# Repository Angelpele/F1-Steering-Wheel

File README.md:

# 🏎️ F1 Steering Wheel

This project is a **custom-made F1-style steering wheel** designed and built entirely from scratch, featuring a **custom PCB**, advanced input/output handling, and a rigid mechanical structure optimized for sim racing or small racing karts.

---

## 🛠️ Electronics & PCB Design

The steering wheel is built around a **custom-designed PCB** using an **ESP32-C6 DevKitC-1** as the main controller, providing high performance and wireless capabilities.

### Main Electronic Features

| Component | Description |
|---------|-------------|
| **ESP32-C6 DevKitC-1** | Main microcontroller handling inputs, logic, and communication |
| **74LS154 Decoder** | 4-to-16 line decoder used to drive LED array |
| **15 LEDs (RGB Groups)** | Divided into 3 groups of 5 LEDs (Green, Red, Blue) |
| **4-Digit 7-Segment Display** | Displays speed, gear, or system information |
| **8 Buttons (Resistor Ladder)** | All buttons read through a single ADC pin |
| **2 Potentiometers** | Center mounted, using voltage divider for analog input |
| **Buzzer** | Return sound feedback to the user reacting to different variables |
| **External Sensor Support** | Designed for external NTC temperature sensor and Hall-effect sensor inputs|
| **Custom Buttons PCB** | Top-mounted buttons integrated into the housing |

The **15 LEDs**, controlled via the **74LS154 decoder**, provide real-time visual feedback:
- **Green LEDs** → Speed or system status  
- **Red LEDs** → Engine RPM / rev-up indication  
- **Blue LEDs** → Custom functions or gear indicators  

The decoder uses **4 control lines** to efficiently manage all LED outputs.

The **8 buttons** are arranged with a resistor ladder configuration, reading all the possible values with an ADC converter (analog input).

📄 Find the **Circuit Schematic** right below:

<p align="center">
  
</p>

---

## ⚙️ Mechanical Design

The entire mechanical structure was **designed from scratch in Fusion 360**, prioritizing rigidity, modularity, and professional finish.

### Structural Overview

1. **Lower Case**
   - Houses most electronic components.
   - Rear sockets allow bolts to be inserted flush with the surface.
   - Enables clean and solid assembly.

2. **Steel Reinforcement Plate**
   - Water-jet cut steel middle plate.
   - Provides structural rigidity and torsional strength.
   - Acts as the main load-bearing core.

3. **TPU Handles**
   - Designed in **two parts per side**.
   - Bolted directly to the internal steel structure.
   - Flexible yet durable for comfortable grip.

4. **PCB Mounting**
   - Custom PCB is mounted on top of the steel plate.
   - Electrically isolated to prevent short circuits.
   - Secured using threaded inserts.

5. **Top Case & Buttons**
   - Top enclosure holds the custom-made buttons.
   - Assembled using **threaded inserts melted into the plastic**.
   - All components are bolted together for maximum durability.

---

## 🚀 Project Goals

- Realistic **F1-style input device**
- Robust **mechanical and electrical integration**
- Support for additional external sensors
- Internal steel structure for proper soldering to external axes

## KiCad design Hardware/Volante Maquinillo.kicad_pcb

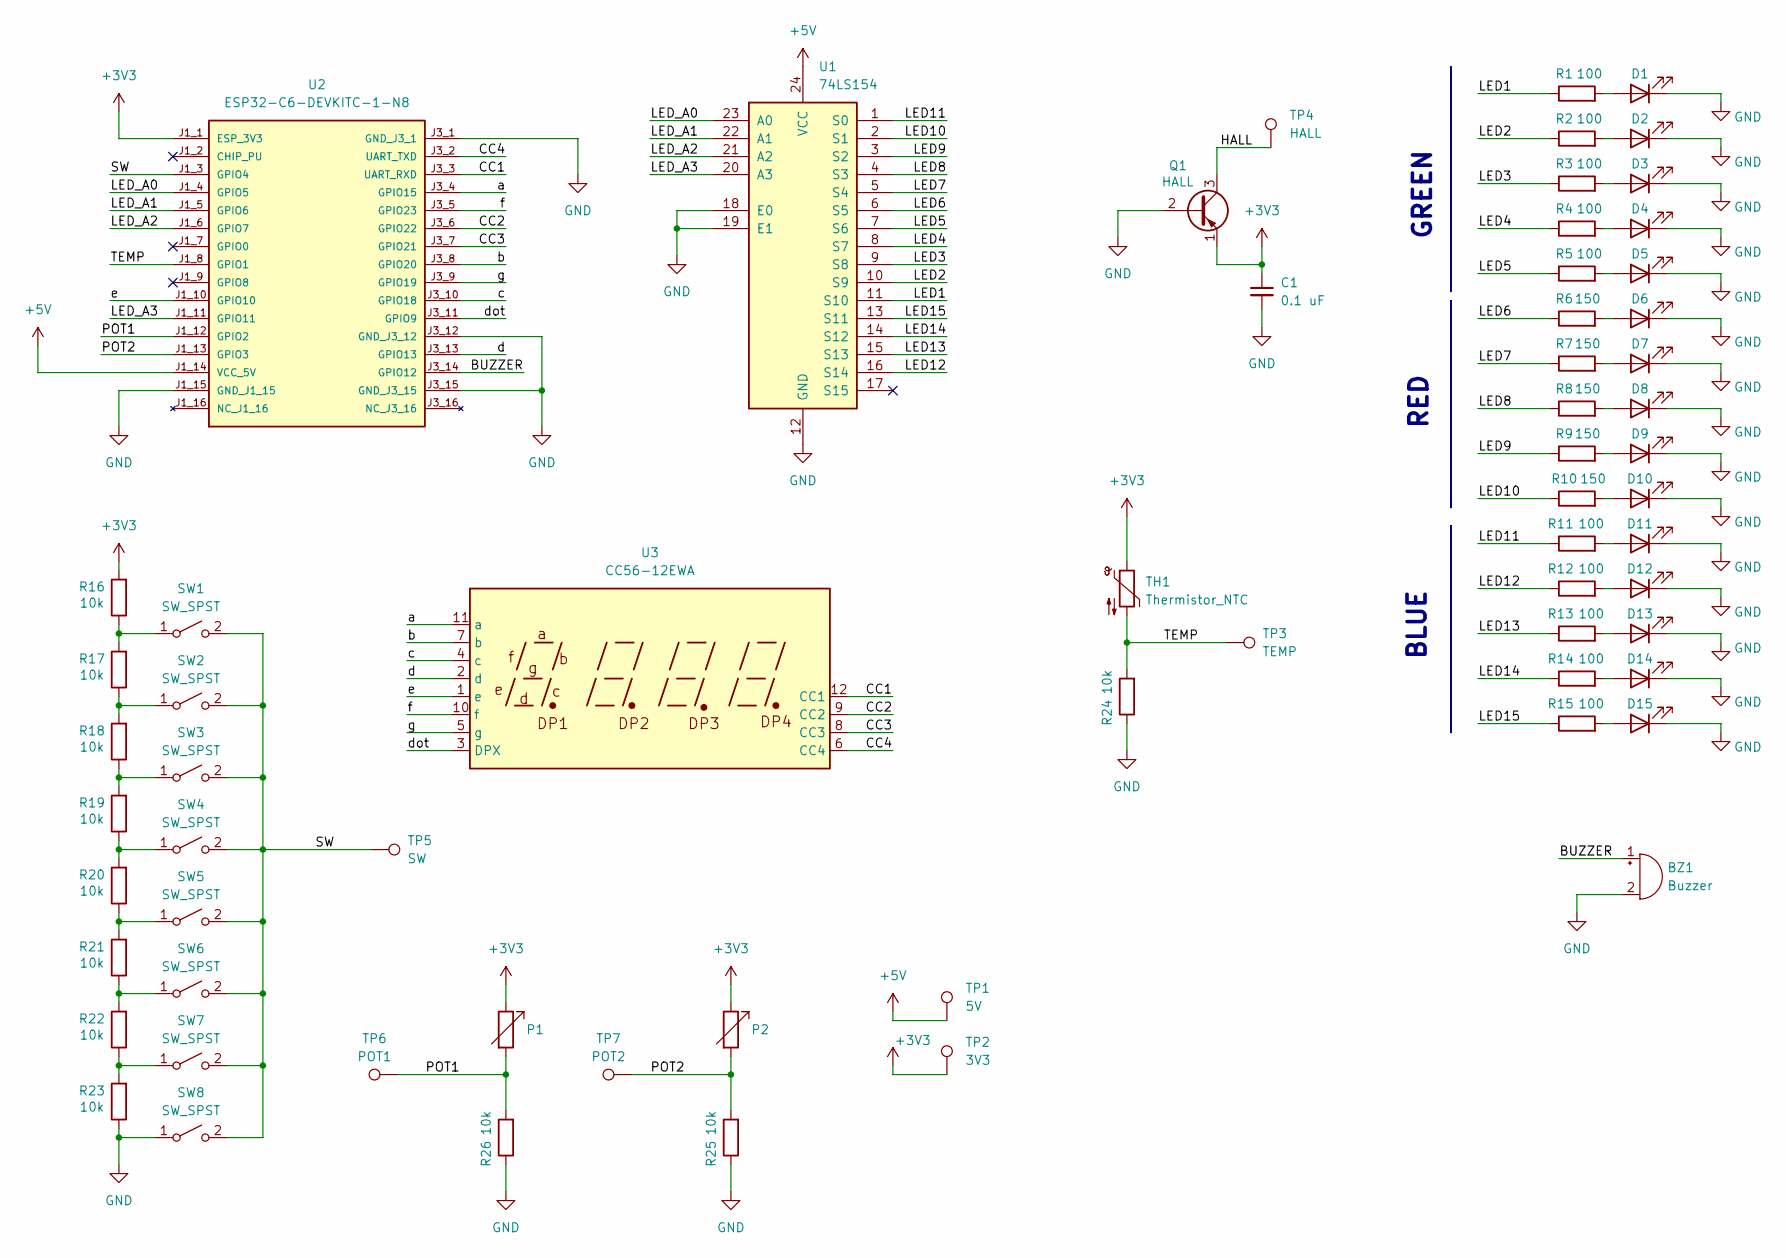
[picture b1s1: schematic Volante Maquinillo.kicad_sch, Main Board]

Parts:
BZ1: Buzzer; Buzzer_12x9.5RM7.6
C1: 0.1 uF; C_0805_2012Metric
D1, D2, D3, D4, D5, D6, D7, D8, D9, D10, D11, D12, D13, D14, D15: LED; LED_Cree-PLCC4_3.2x2.8mm_CCW
P1, P2: R_Variable; Potentiometer_ACP_CA9-V10_Vertical_Hole
Q1: HALL; TO-92Flat
R1, R2, R3, R4, R5, R11, R12, R13, R14, R15: 100; R_0805_2012Metric
R6, R7, R8, R9, R10: 150; R_0805_2012Metric
R16, R17, R18, R19, R20, R21, R22, R23, R24, R25, R26: 10k; R_0805_2012Metric
SW1, SW2, SW3, SW4, SW5, SW6, SW7, SW8: SW_SPST; SW_TS02-66-60-BK-100-LCR-D
TH1: Thermistor_NTC; PinHeader_1x02_P2.54mm_Vertical
TP1: 5V; TestPoint_Pad_D1.0mm
TP2: 3V3; TestPoint_Pad_D1.0mm
TP3: TEMP; TestPoint_Pad_D1.0mm
TP4: HALL; TestPoint_Pad_D1.0mm
TP5: SW; TestPoint_Pad_D1.0mm
TP6: POT1; TestPoint_Pad_D1.0mm
TP7: POT2; TestPoint_Pad_D1.0mm
U1: 74LS154; TSSOP-24_4.4x7.8mm_P0.65mm
U2: ESP32-C6-DEVKITC-1-N8; MODULE_ESP32-C6-DEVKITC-1-N8; PARTREV 1.3
U3: CC56-12EWA; CA56-12EWA

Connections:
+3V3: C1.1, P1.1, P2.1, Q1.1 (E), R16.2, TH1.1, TP2.1, U2.J1_1 (ESP_3V3)
+5V: TP1.1, U1.24 (VCC), U2.J1_14 (VCC_5V)
/BUZZER: BZ1.1 (+), U2.J3_14 (GPIO12)
/CC1: U2.J3_3 (UART_RXD), U3.12 (CC1)
/CC2: U2.J3_6 (GPIO22), U3.9 (CC2)
/CC3: U2.J3_7 (GPIO21), U3.8 (CC3)
/CC4: U2.J3_2 (UART_TXD), U3.6 (CC4)
/HALL: Q1.3 (C), TP4.1
/LED1: R1.1, U1.11 (S10)
/LED2: R2.1, U1.10 (S9)
/LED3: R3.1, U1.9 (S8)
/LED4: R4.1, U1.8 (S7)
/LED5: R5.1, U1.7 (S6)
/LED6: R6.1, U1.6 (S5)
/LED7: R7.1, U1.5 (S4)
/LED8: R8.1, U1.4 (S3)
/LED9: R9.1, U1.3 (S2)
/LED10: R10.1, U1.2 (S1)
/LED11: R11.1, U1.1 (S0)
/LED12: R12.1, U1.16 (S14)
/LED13: R13.1, U1.15 (S13)
/LED14: R14.1, U1.14 (S12)
/LED15: R15.1, U1.13 (S11)
/LED_A0: U1.23 (A0), U2.J1_4 (GPIO5)
/LED_A1: U1.22 (A1), U2.J1_5 (GPIO6)
/LED_A2: U1.21 (A2), U2.J1_6 (GPIO7)
/LED_A3: U1.20 (A3), U2.J1_11 (GPIO11)
/POT1: P1.2, R26.2, TP6.1, U2.J1_12 (GPIO2)
/POT2: P2.2, R25.2, TP7.1, U2.J1_13 (GPIO3)
/SW: SW1.2 (B), SW2.2 (B), SW3.2 (B), SW4.2 (B), SW5.2 (B), SW6.2 (B), SW7.2 (B), SW8.2 (B), TP5.1, U2.J1_3 (GPIO4)
/TEMP: R24.2, TH1.2, TP3.1, U2.J1_8 (GPIO1)
/a: U2.J3_4 (GPIO15), U3.11 (a)
/b: U2.J3_8 (GPIO20), U3.7 (b)
/c: U2.J3_10 (GPIO18), U3.4 (c)
/d: U2.J3_13 (GPIO13), U3.2 (d)
/dot: U2.J3_11 (GPIO9), U3.3 (DPX)
/e: U2.J1_10 (GPIO10), U3.1 (e)
/f: U2.J3_5 (GPIO23), U3.10 (f)
/g: U2.J3_9 (GPIO19), U3.5 (g)
GND: BZ1.2 (-), C1.2, D1.1 (K), D2.1 (K), D3.1 (K), D4.1 (K), D5.1 (K), D6.1 (K), D7.1 (K), D8.1 (K), D9.1 (K), D10.1 (K), D11.1 (K), D12.1 (K), D13.1 (K), D14.1 (K), D15.1 (K), Q1.2 (B), R23.1, R24.1, R25.1, R26.1, SW8.1 (A), U1.12 (GND), U1.18 (E0), U1.19 (E1), U2.J1_15 (GND_J1_15), U2.J3_1 (GND_J3_1), U2.J3_12 (GND_J3_12), U2.J3_15 (GND_J3_15)
unnamed: D1.2 (A), R1.2
unnamed: D2.2 (A), R2.2
unnamed: D3.2 (A), R3.2
unnamed: D4.2 (A), R4.2
unnamed: D5.2 (A), R5.2
unnamed: D6.2 (A), R6.2
unnamed: D7.2 (A), R7.2
unnamed: D8.2 (A), R8.2
unnamed: D9.2 (A), R9.2
unnamed: D10.2 (A), R10.2
unnamed: D11.2 (A), R11.2
unnamed: D12.2 (A), R12.2
unnamed: D13.2 (A), R13.2
unnamed: D14.2 (A), R14.2
unnamed: D15.2 (A), R15.2
unnamed: R16.1, R17.2, SW1.1 (A)
unnamed: R17.1, R18.2, SW2.1 (A)
unnamed: R18.1, R19.2, SW3.1 (A)
unnamed: R19.1, R20.2, SW4.1 (A)
unnamed: R20.1, R21.2, SW5.1 (A)
unnamed: R21.1, R22.2, SW6.1 (A)
unnamed: R22.1, R23.2, SW7.1 (A)

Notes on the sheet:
RED
BLUE
GREEN

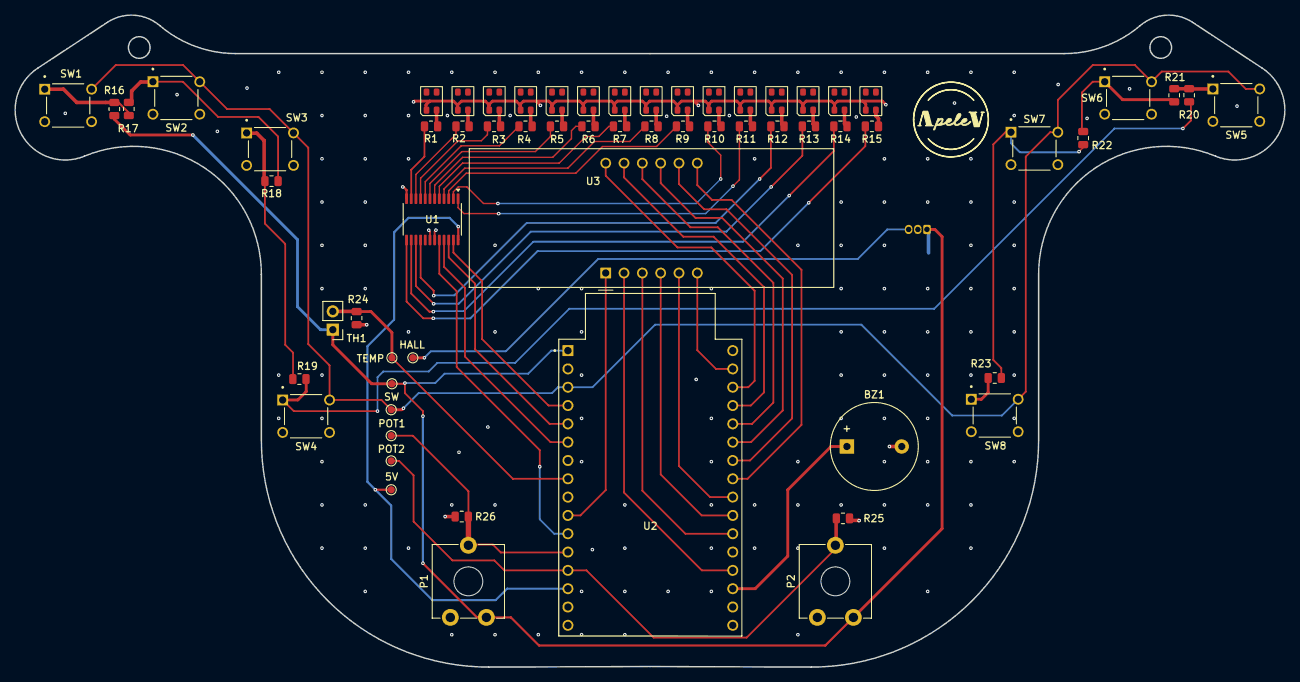
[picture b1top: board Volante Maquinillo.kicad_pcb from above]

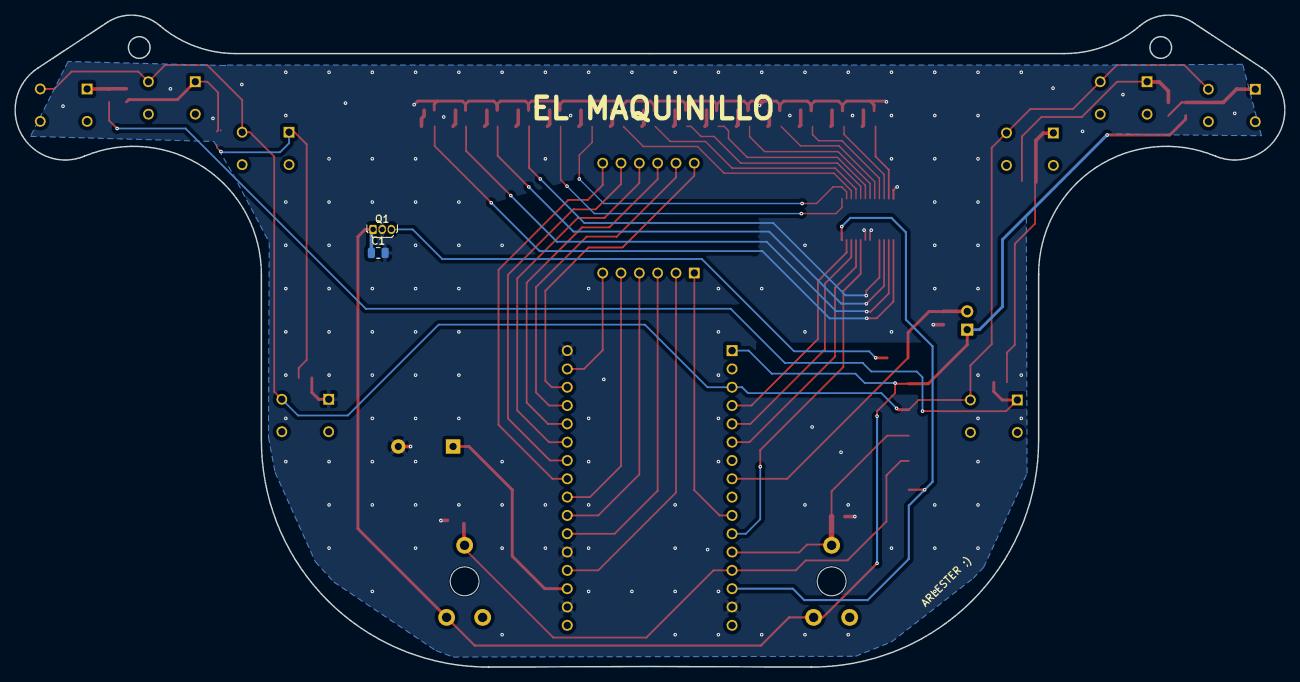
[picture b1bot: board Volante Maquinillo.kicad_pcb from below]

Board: 2 copper layers, 176.1 x 90.4 mm, 65 parts (2 on the bottom side), 62 nets.

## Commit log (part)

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2026-02-07 Media update
2026-02-07 README update
    Expanded README to include detailed project description, electronics and PCB design, mechanical design, user interface, project goals, and future improvements.
2026-02-07 Update README
    Updated project description, image paths, and component details.
2026-02-07 Include SCH README
    Added a section for the Circuit Schematic with a link and image.
